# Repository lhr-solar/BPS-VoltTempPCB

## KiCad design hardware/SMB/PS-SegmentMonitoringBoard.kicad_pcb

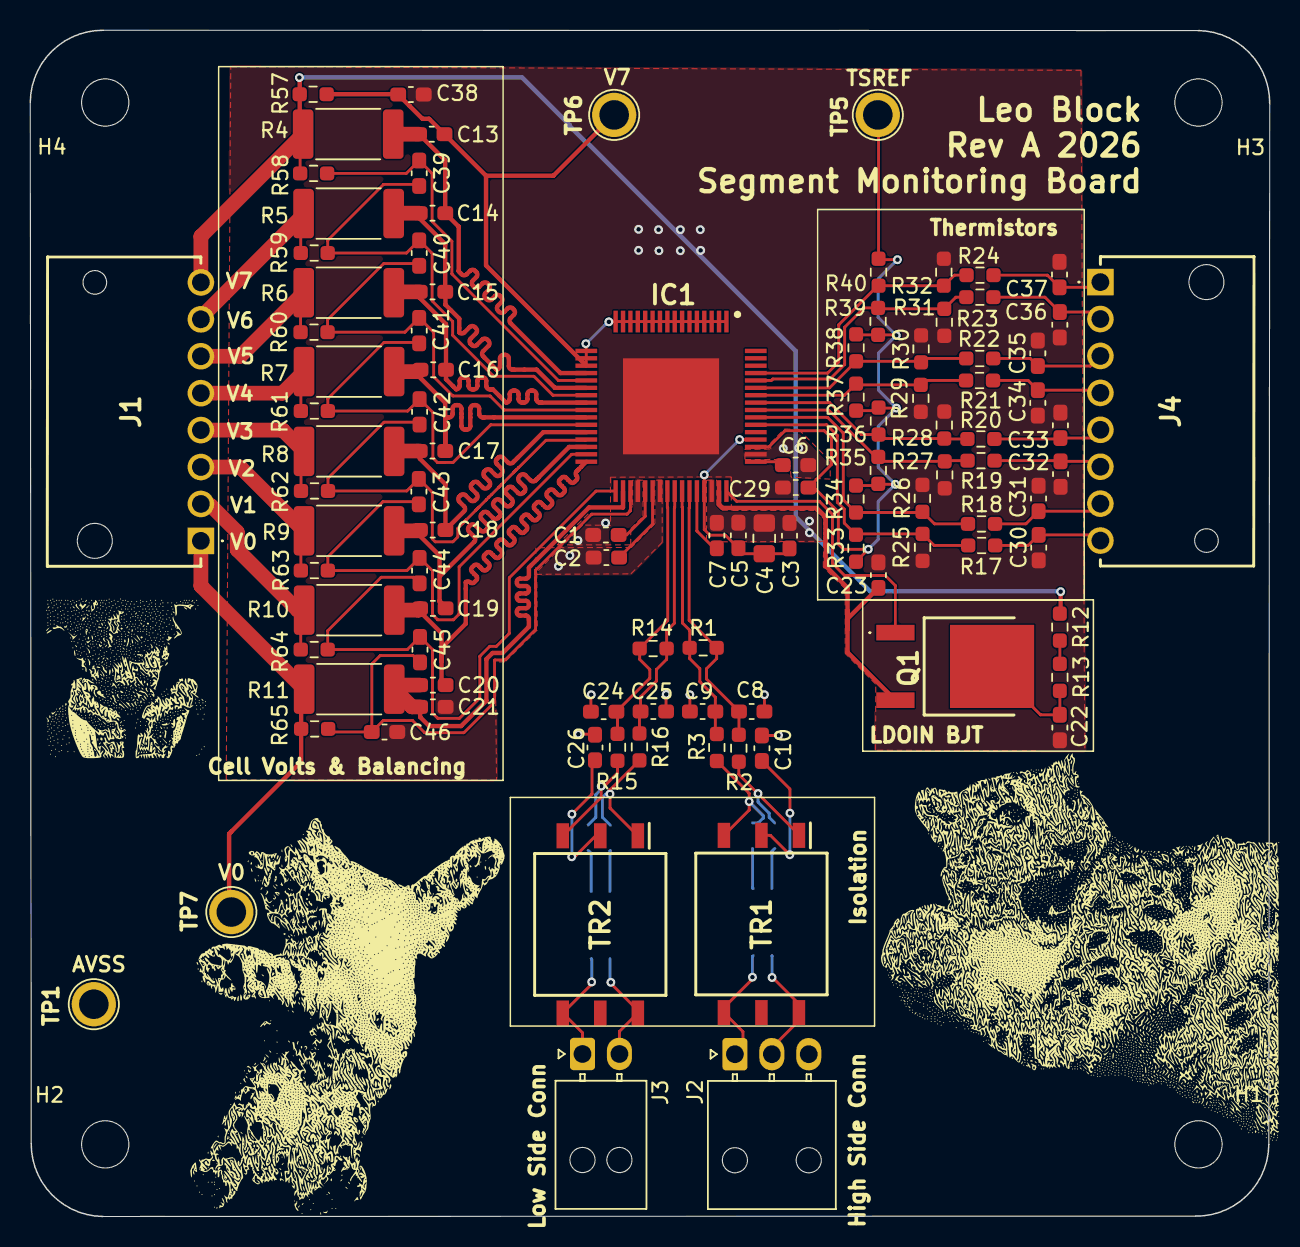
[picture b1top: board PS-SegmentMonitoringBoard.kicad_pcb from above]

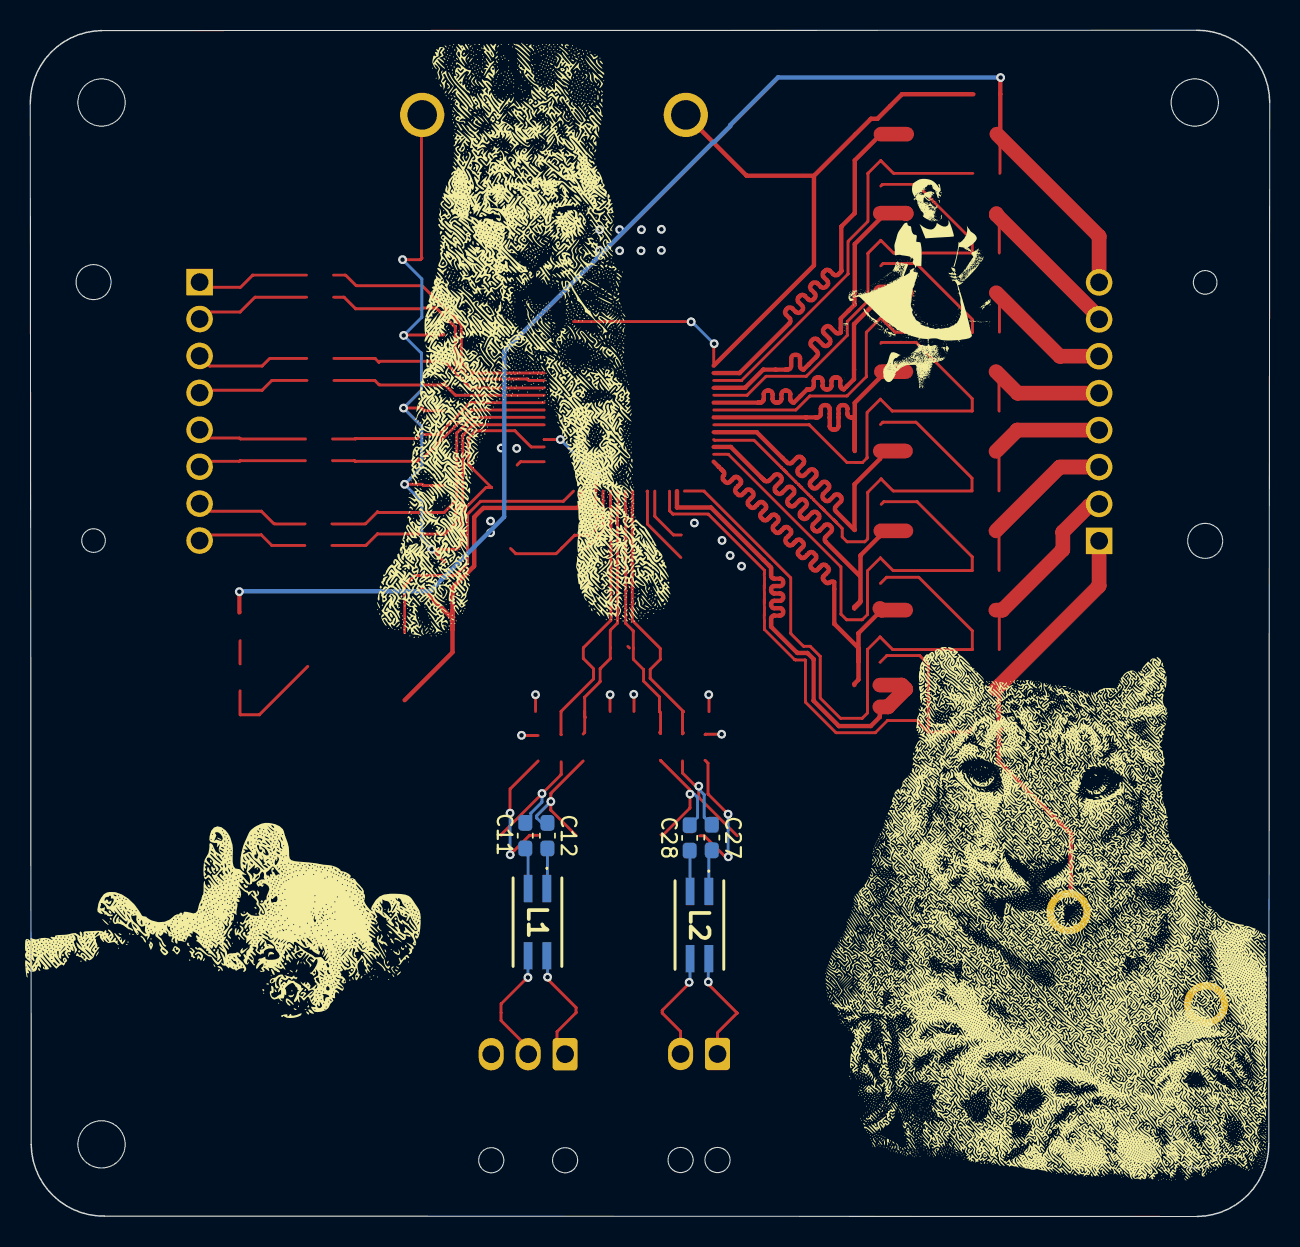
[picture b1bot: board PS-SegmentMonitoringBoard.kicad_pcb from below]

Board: 4 copper layers, 83.9 x 80.3 mm, 114 parts (6 on the bottom side), 70 nets.

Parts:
C1, C2, C29, C30, C31, C32, C33, C34, C35, C36, C37: 1uF; C_0603_1608Metric_Pad1.08x0.95mm_HandSolder
C3: 22nF; C_0603_1608Metric_Pad1.08x0.95mm_HandSolder
C4: 4.7uF; C_0805_2012Metric_Pad1.18x1.45mm_HandSolder
C5: 100nF; C_0603_1608Metric_Pad1.08x0.95mm_HandSolder
C6: 2.2uF; C_0603_1608Metric_Pad1.08x0.95mm_HandSolder
C7, C23: 0.1uF; C_0603_1608Metric_Pad1.08x0.95mm_HandSolder
C8, C9, C11, C12, C24, C25, C27, C28: 220pF; C_0603_1608Metric_Pad1.08x0.95mm_HandSolder
C10, C26: 100pF; C_0603_1608Metric_Pad1.08x0.95mm_HandSolder
C13, C14, C15, C16, C17, C18, C19, C20, C21, C39, C40, C41, C42, C43, C44, C45, C46: 0.47uF; C_0603_1608Metric_Pad1.08x0.95mm_HandSolder
C22: 0.22uF; C_0603_1608Metric_Pad1.08x0.95mm_HandSolder
C38: 10nF; C_0603_1608Metric_Pad1.08x0.95mm_HandSolder
H1, H2, H3, H4: MountingHole; MountingHole_3.2mm_M3
IC1: BQ79616PAPR; QFP50P1200X1200X120-65N
J1: voltTapsConn; Molex_Nano-Fit_105313-xx08_1x08_P2.50mm_Horizontal
J2: highSideConn; Molex_Nano-Fit_105313-xx03_1x03_P2.50mm_Horizontal
J3: lowSideConn; Molex_Nano-Fit_105313-xx02_1x02_P2.50mm_Horizontal
J4: thermsConn; Molex_Nano-Fit_105313-xx08_1x08_P2.50mm_Horizontal
L1, L2: L_Coupled_1423; 744242471
LOGO1: Dr. Hallock; LHRs_LOGO
Q1: ZXTN4004KTC
R1, R14, R17, R18, R19, R20, R21, R22, R23, R24: 1k; R_0603_1608Metric_Pad0.98x0.95mm_HandSolder
R2, R3, R15, R16: 49; R_0603_1608Metric_Pad0.98x0.95mm_HandSolder
R4, R5, R6, R7, R8, R9, R10, R11: 6.2; R_2512_6332Metric_Pad1.40x3.35mm_HandSolder
R12: 200; R_0603_1608Metric_Pad0.98x0.95mm_HandSolder
R13, R58, R59, R60, R61, R62, R63, R64, R65: 100; R_0603_1608Metric_Pad0.98x0.95mm_HandSolder
R25, R26, R27, R28, R29, R30, R31, R32: 15k; R_0603_1608Metric_Pad0.98x0.95mm_HandSolder
R33, R34, R35, R36, R37, R38, R39, R40: 3.6k; R_0603_1608Metric_Pad0.98x0.95mm_HandSolder
R57: 30; R_0603_1608Metric_Pad0.98x0.95mm_HandSolder
TP1: AVSS; TestPoint_Plated_Hole_D2.0mm
TP5: TSREF; TestPoint_Plated_Hole_D2.0mm
TP6: V7; TestPoint_Plated_Hole_D2.0mm
TP7: V0; TestPoint_Plated_Hole_D2.0mm
TR1, TR2: HMU1228NL; SOP254P1270X685-6N

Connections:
/CB0: C20.2, C21.1, IC1.34 (CB0), R11.2
/CB1: C19.2, C20.1, IC1.32 (CB1), R10.2
/CB2: C18.2, C19.1, IC1.30 (CB2), R9.2
/CB3: C17.2, C18.1, IC1.28 (CB3), R8.2
/CB4: C16.2, C17.1, IC1.26 (CB4), R7.2
/CB5: C15.2, C16.1, IC1.24 (CB5), R6.2
/CB6: C14.2, C15.1, IC1.22 (CB6), R5.2
/CB7: C13.2, C14.1, IC1.20 (CB7), R4.2
/CVDD: C3.1, C4.1, C5.1, IC1.45 (CVDD), IC1.52 (RX)
/Cell_Balancing/V0: J1.1, R11.1, R65.1, TP7.1 (1_1)
/Cell_Balancing/V1: J1.2, R10.1, R64.1
/Cell_Balancing/V2: J1.3, R9.1, R63.1
/Cell_Balancing/V3: J1.4, R8.1, R62.1
/Cell_Balancing/V4: J1.5, R7.1, R61.1
/Cell_Balancing/V5: J1.6, R6.1, R60.1
/Cell_Balancing/V6: J1.7, R5.1, R59.1
/Cell_Balancing/V7: J1.8, R4.1, R12.1, R57.2, R58.1
/LDOIN_NPN/LDOIN: C23.1, IC1.47 (LDOIN), Q1.3 (E)
/LDOIN_NPN/NPNB: IC1.48 (NPNB), Q1.1 (B)
/TSREF: C29.1, IC1.51 (TSREF), R33.2, R34.2, R35.2, R36.2, R37.2, R38.2, R39.2, R40.2, TP5.1 (1_1)
/Thermistors/NTC0: IC1.61 (GPIO1), R24.1, R32.2, R40.1
/Thermistors/NTC1: IC1.60 (GPIO2), R23.1, R31.2, R39.1
/Thermistors/NTC2: IC1.59 (GPIO3), R22.1, R30.2, R38.1
/Thermistors/NTC3: IC1.58 (GPIO4), R21.1, R29.2, R37.1
/Thermistors/NTC4: IC1.57 (GPIO5), R20.1, R28.2, R36.1
/Thermistors/NTC5: IC1.56 (GPIO6), R19.1, R27.2, R35.1
/Thermistors/NTC6: IC1.55 (GPIO7), R18.1, R26.2, R34.1
/Thermistors/NTC7: IC1.54 (GPIO8), R17.1, R25.2, R33.1
/Thermistors/TEMP_0: C37.1, J4.1, R24.2
/Thermistors/TEMP_1: C36.1, J4.2, R23.2
/Thermistors/TEMP_2: C35.1, J4.3, R22.2
/Thermistors/TEMP_3: C34.1, J4.4, R21.2
/Thermistors/TEMP_4: C33.1, J4.5, R20.2
/Thermistors/TEMP_5: C32.1, J4.6, R19.2
/Thermistors/TEMP_6: C31.1, J4.7, R18.2
/Thermistors/TEMP_7: C30.1, J4.8, R17.2
/Volt_Taps/VC0: C45.2, C46.1, IC1.35 (VC0), R65.2
/Volt_Taps/VC1: C44.2, C45.1, IC1.33 (VC1), R64.2
/Volt_Taps/VC2: C43.2, C44.1, IC1.31 (VC2), R63.2
/Volt_Taps/VC3: C42.2, C43.1, IC1.29 (VC3), R62.2
/Volt_Taps/VC4: C41.2, C42.1, IC1.27 (VC4), R61.2
/Volt_Taps/VC5: C40.2, C41.1, IC1.25 (VC5), R60.2
/Volt_Taps/VC6: C39.2, C40.1, IC1.23 (VC6), R59.2
/Volt_Taps/VC7: C39.1, IC1.21 (VC7), R58.2
/extraCells: C13.1, C38.2, IC1.1 (BAT), IC1.2 (CB16), IC1.3 (VC16), IC1.4 (CB15), IC1.5 (VC15), IC1.6 (CB14), IC1.7 (VC14), IC1.8 (CB13), IC1.9 (VC13), IC1.10 (CB12), IC1.11 (VC12), IC1.12 (CB11), IC1.13 (VC11), IC1.14 (CB10), IC1.15 (VC10), IC1.16 (CB9), IC1.17 (VC9), IC1.18 (CB8), IC1.19 (VC8), R57.1, TP6.1 (1_1)
/highSideIsolation/COMHN: C9.1, IC1.42 (COMHN), R1.2, R3.1
/highSideIsolation/COMHP: C8.1, IC1.43 (COMHP), R1.1, R2.1
/highSideIsolation/isolatedCOMHN: J2.1, L1.4, TR1.4
/highSideIsolation/isolatedCOMHP: J2.2, L1.3, TR1.6
/highSideIsolation/preIsolationCOMHN: C12.1, R3.2, TR1.3
/highSideIsolation/preIsolationCOMHP: C11.1, R2.2, TR1.1
/lowSideIsolation/COMLN: C25.1, IC1.41 (COMLN), R14.2, R16.1
/lowSideIsolation/COMLP: C24.1, IC1.40 (COMLP), R14.1, R15.1
/lowSideIsolation/isolatedCOMLN: J3.2, L2.3, TR2.6
/lowSideIsolation/isolatedCOMLP: J3.1, L2.4, TR2.4
/lowSideIsolation/preIsolationCOMHN: C28.1, R16.2, TR2.1
/lowSideIsolation/preIsolationCOMHP: C27.1, R15.2, TR2.3
AVSS: C1.2, C2.2, C3.2, C4.2, C5.2, C6.2, C7.1, C8.2, C9.2, C10.1, C21.2, C22.2, C23.2, C24.2, C25.2, C26.1, C29.2, C30.2, C31.2, C32.2, C33.2, C34.2, C35.2, C36.2, C37.2, C38.1, C46.2, IC1.36 (REFHM), IC1.39 (AVSS), IC1.46 (CVSS), IC1.50 (DVSS), IC1.65 (PAD), R25.1, R26.1, R27.1, R28.1, R29.1, R30.1, R31.1, R32.1, TP1.1 (1_1)
unnamed: C10.2, TR1.2
unnamed: C11.2, L1.2
unnamed: C12.2, L1.1
unnamed: C26.2, TR2.2
unnamed: C27.2, L2.1
unnamed: C28.2, L2.2
unnamed: C2.1, IC1.38 (AVDD)
unnamed: C6.1, IC1.49 (DVDD)
unnamed: C7.2, IC1.44 (NEG5V)
unnamed: C1.1, IC1.37 (REFHP)
unnamed: C22.1, Q1.2 (C), R13.2
unnamed: R12.2, R13.1

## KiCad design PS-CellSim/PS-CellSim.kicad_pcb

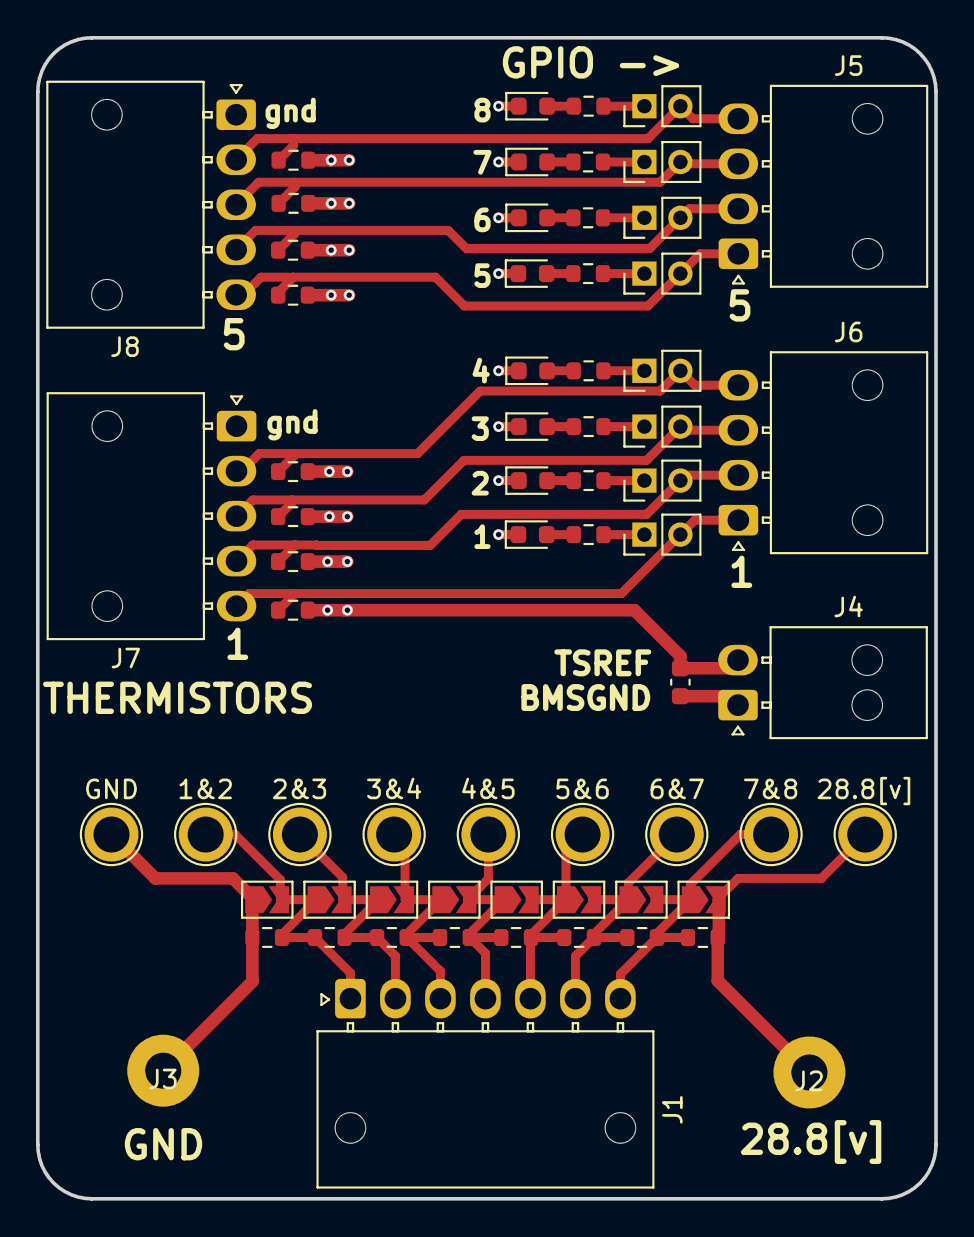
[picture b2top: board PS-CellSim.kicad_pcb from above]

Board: 2 copper layers, 49.9 x 64.5 mm, 66 parts (0 on the bottom side), 35 nets.

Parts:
1&2, 2&3, 3&4, 4&5, 5&6, 6&7, 7&8, 28.8[v]: TestPoint; TestPoint_Plated_Hole_D2.0mm
C1: 1 uF; C_0603_1608Metric
D1, D2, D3, D4, D5, D6, D7, D8: LED; LED_0603_1608Metric
GND: TestPoint; TestPoint_Plated_Hole_D2.0mm
J1: bms_taps; Molex_Nano-Fit_105313-xx07_1x07_P2.50mm_Horizontal
J2: bench_vcc; Banana_Jack_1_Pin_4mm
J3: bench_gnd; Banana_Jack_1_Pin_4mm
J4: bms_ref; Molex_Nano-Fit_105313-xx02_1x02_P2.50mm_Horizontal
J5: bms_gpio_set2; Molex_Nano-Fit_105313-xx04_1x04_P2.50mm_Horizontal
J6: bms_gpio_set1; Molex_Nano-Fit_105313-xx04_1x04_P2.50mm_Horizontal
J7: therm_set1; Molex_Nano-Fit_105313-xx05_1x05_P2.50mm_Horizontal
J8: therm_set2; Molex_Nano-Fit_105313-xx05_1x05_P2.50mm_Horizontal
JP1, JP2, JP3, JP4, JP5, JP6, JP7, JP8: SolderJumper_2_Open; SolderJumper-2_P1.3mm_Open_TrianglePad1.0x1.5mm
JP9, JP10, JP11, JP12, JP13, JP14, JP15, JP16: Jumper; PinHeader_1x02_P2.00mm_Vertical
R1, R2, R3, R4, R5, R6, R7, R8: 50Ω; R_0603_1608Metric
R9, R11, R13, R15, R17, R19, R21, R23: 10 kΩ; R_0603_1608Metric
R10, R12, R14, R16, R18, R20, R22, R24: 250 Ω; R_0603_1608Metric

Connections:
+5V: C1.1, J4.2, R9.1, R11.1, R13.1, R15.1, R17.1, R19.1, R21.1, R23.1
/1&2: 1&2.1 (1_1), J1.1, JP1.2 (B), JP2.1 (A), R1.1, R2.2
/2&3: 2&3.1 (1_1), J1.2, JP2.2 (B), JP3.1 (A), R2.1, R3.2
/3&4: 3&4.1 (1_1), J1.3, JP3.2 (B), JP4.1 (A), R3.1, R4.2
/4&5: 4&5.1 (1_1), J1.4, JP4.2 (B), JP5.1 (A), R4.1, R5.2
/5&6: 5&6.1 (1_1), J1.5, JP5.2 (B), JP6.1 (A), R5.1, R6.2
/6&7: 6&7.1 (1_1), J1.6, JP6.2 (B), JP7.1 (A), R6.1, R7.2
/7&8: 7&8.1 (1_1), J1.7, JP7.2 (B), JP8.1 (A), R7.1, R8.2
/GPIO1: J6.1, J7.5, JP9.2 (B), R9.2
/GPIO2: J6.2, J7.4, JP10.2 (B), R11.2
/GPIO3: J6.3, J7.3, JP11.2 (B), R13.2
/GPIO4: J6.4, J7.2, JP12.2 (B), R15.2
/GPIO5: J5.1, J8.5, JP13.2 (B), R17.2
/GPIO6: J5.2, J8.4, JP14.2 (B), R19.2
/GPIO7: J5.3, J8.3, JP15.2 (B), R21.2
/GPIO8: J5.4, J8.2, JP16.2 (B), R23.2
GND: GND.1 (1_1), J3.1 (Pin_1_1), JP1.1 (A), R1.2
GND1: C1.2, D1.1 (K), D2.1 (K), D3.1 (K), D4.1 (K), D5.1 (K), D6.1 (K), D7.1 (K), D8.1 (K), J4.1, J7.1, J8.1
unnamed: D1.2 (A), R10.1
unnamed: D2.2 (A), R12.1
unnamed: D3.2 (A), R14.1
unnamed: D4.2 (A), R16.1
unnamed: D5.2 (A), R18.1
unnamed: D6.2 (A), R20.1
unnamed: D7.2 (A), R22.1
unnamed: D8.2 (A), R24.1
unnamed: JP9.1 (A), R10.2
unnamed: JP10.1 (A), R12.2
unnamed: JP11.1 (A), R14.2
unnamed: JP12.1 (A), R16.2
unnamed: JP13.1 (A), R18.2
unnamed: JP14.1 (A), R20.2
unnamed: JP15.1 (A), R22.2
unnamed: JP16.1 (A), R24.2
VCC: 28.8[v].1 (1_1), J2.1 (Pin_1_1), JP8.2 (B), R8.1

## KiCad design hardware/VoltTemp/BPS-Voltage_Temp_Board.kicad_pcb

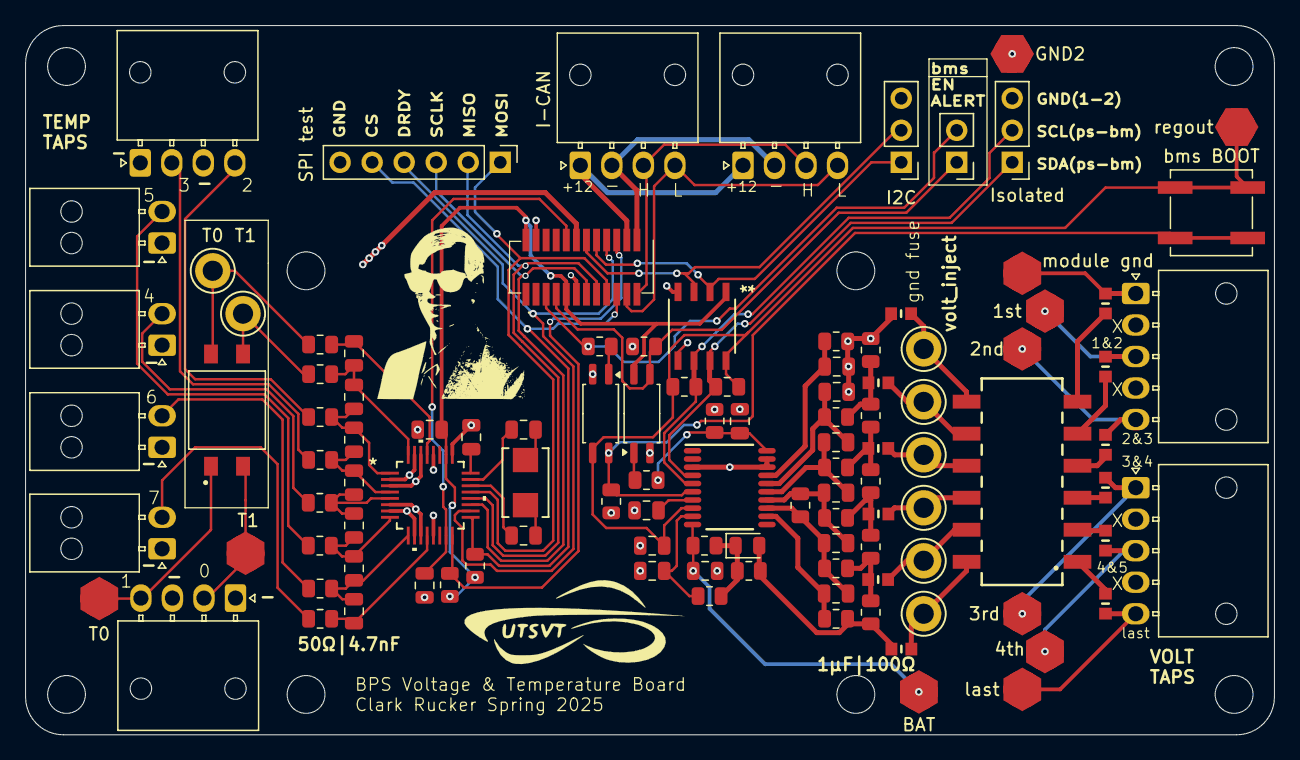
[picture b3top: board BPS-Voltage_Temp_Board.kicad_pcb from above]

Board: 2 copper layers, 99.0 x 56.2 mm, 115 parts (0 on the bottom side), 82 nets.

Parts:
1st: 1&2 COM; TestPoint_HEX_3mmID
2nd: 2&3 COM; TestPoint_HEX_3mmID
3rd: 3&4 COM; TestPoint_HEX_3mmID
4th: 4&5 COM; TestPoint_HEX_3mmID
BAT: BAT tap; TestPoint_HEX_3mmID
C1: 4.7pF; C_0805_2012Metric
C2: 10μF; C_0805_2012Metric
C3, C5, C6, C7, C8, C9, C10, C11, C19, C20: 1μF; C_0805_2012Metric
C4: 4.7μF; C_0805_2012Metric
C12, C13, C14, C15, C16, C17, C18: 4.7nF; C_0805_2012Metric
C21: 220nF; C_0805_2012Metric
C22, C23: 18pF; C_0805_2012Metric
D1: D_Zener_Small; D_0805_2012Metric
F1, F2, F3, F4, F5, F7, F8, F9, F10, F11: 10mA; ptc_fuse_FUSC1607X75N
F6, F12: 40mA; ptc_fuse_FUSC1607X75N
GND2: VSS tap; TestPoint_HEX_3mmID
H1, H1#2, H1#3, H1#4: MountingHole; MountingHole_3mm
I2C: psom bms i2c test; PinHeader_1x03_P2.54mm_Vertical
I-CAN: I-CAN connector; Molex_Nano-Fit_105313-xx04_1x04_P2.50mm_Horizontal
Isolated: bms i2c test; PinHeader_1x03_P2.54mm_Vertical
J1: VoltTap2; Molex_Nano-Fit_105313-xx05_1x05_P2.50mm_Horizontal
J2: VoltTap1; Molex_Nano-Fit_105313-xx05_1x05_P2.50mm_Horizontal
J6: I-CAN connector; Molex_Nano-Fit_105313-xx04_1x04_P2.50mm_Horizontal
J7: temptap0; Molex_Nano-Fit_105313-xx04_1x04_P2.50mm_Horizontal
J8: temptap1; Molex_Nano-Fit_105313-xx04_1x04_P2.50mm_Horizontal
J9: extratemp1; Molex_Nano-Fit_105313-xx02_1x02_P2.50mm_Horizontal
J10: extratemp3; Molex_Nano-Fit_105313-xx02_1x02_P2.50mm_Horizontal
J11: extratemp2; Molex_Nano-Fit_105313-xx02_1x02_P2.50mm_Horizontal
J12: extratemp4; Molex_Nano-Fit_105313-xx02_1x02_P2.50mm_Horizontal
J14: alert/en_test; PinHeader_1x02_P2.54mm_Vertical
R1, R6, R9, R10: 10kΩ; R_0805_2012Metric
R2: 500kΩ; R_0805_2012Metric
R3, R4, R17, R18, R19, R20, R21, R22: 100Ω; R_0805_2012Metric
R5: 2kΩ; R_0805_2012Metric
R7, R8: 1kΩ; R_0805_2012Metric
R11, R12, R13, R14, R15, R16: 0Ω; R_0805_2012Metric
R23, R24, R25, R26, R27, R28, R29, R30: 50Ω; R_0805_2012Metric
R31, R32: 100kΩ; R_0805_2012Metric
S1: 418121270806
S2: DS04-254-2-02BK-SMT-TR; SW_DS04-254-2-02BK-SMT-TR
SPI test: SPI test; PinHeader_1x06_P2.54mm_Vertical
T0: temp0inject; TestPoint_Keystone_5010-5014_Multipurpose
T0#2: t0test; TestPoint_HEX_3mmID
T1: temp1inject; TestPoint_Keystone_5010-5014_Multipurpose
T1#2: t1test; TestPoint_HEX_3mmID
TP9: last_inject; TestPoint_Keystone_5010-5014_Multipurpose
TP10: 4&5inject; TestPoint_Keystone_5010-5014_Multipurpose
TP11: 3&4inject; TestPoint_Keystone_5010-5014_Multipurpose
TP12: 2&3inject; TestPoint_Keystone_5010-5014_Multipurpose
TP13: 1&2inject; TestPoint_Keystone_5010-5014_Multipurpose
TP14: cellgndinject; TestPoint_Keystone_5010-5014_Multipurpose
U1, U3: EL3H7; SSOP-4_4.4x2.6mm_P1.27mm
U2: BQ7692003PW; PW0020A_N
U4: ISO1641BDR; SOIC8_D_TEX
U5: PeripheralSOM
U6: ADS131M08QPBSRQ1; TQFP32_PBS_TEX
XTAL1: ABM3-8.000MHZ-D2Y-T; XTAL_ABM3-8.000MHZ-D2Y-T_ABR
bms BOOT: BMS_BOOT; SW_SPST_B3SL-1002P
last: last_cell; TestPoint_HEX_3mmID
module gnd: GND2; TestPoint_HEX_3mmID
regout: regout testpoint; TestPoint_HEX_3mmID

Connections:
+3.3V: C20.1, R31.1, R32.2, U1.4, U4.1 (VCC1), U5.2 (+3.3V), U5.9 (+3.3V), U6.26 (DVDD)
+3.3VA: C19.1, U5.10 (VDDA(3.3V)), U6.15 (AVDD)
+12V: I-CAN.1 (12V), J6.1 (12V), U5.22 (+12V_In)
/1&2COM: F11.2, R15.2, R16.1, R21.2
/2&3COM: F10.2, R14.2, R15.1, R20.2
/3&4COM: F9.2, R13.2, R14.1, R19.2
/4&5COM: F8.2, R12.2, R13.1, R18.2
/BMSboot: R6.2, U2.6 (TS1), U3.4, bms BOOT.2
/DRDY: SPI test.4, U5.18 (PA2(ADC)), U6.18 (*DRDY)
/I-CAN_H: I-CAN.3 (CAN_H), J6.3 (CAN_H), U5.23 (CAN_H)
/I-CAN_L: I-CAN.4 (CAN_L), J6.4 (CAN_L), U5.21 (CAN_L)
/SYNC: R31.2, U5.20 (PA1(ADC)), U6.16 (*SYNC/*RESET)
/Thermistor town/AIN0: C18.1, R30.1, U6.29 (AIN0P)
/Thermistor town/AIN1: C17.1, C18.2, R29.1, U6.32 (AIN1P)
/Thermistor town/AIN2: C16.1, C17.2, R28.1, U6.1 (AIN2P)
/Thermistor town/AIN3: C15.1, C16.2, R27.1, U6.4 (AIN3P)
/Thermistor town/AIN4: C14.1, C15.2, R26.1, U6.5 (AIN4P)
/Thermistor town/AIN5: C13.1, C14.2, R25.1, U6.8 (AIN5P)
/Thermistor town/AIN6: C12.1, C13.2, R24.1, U6.9 (AIN6P)
/Thermistor town/AIN7: C12.2, R23.1, U6.12 (AIN7P)
/Thermistor town/temp0: R30.2, S2.1B, T0.1
/Thermistor town/temp1: R29.2, S2.2B, T1.1
/Thermistor town/temp2: J8.4, R28.2
/Thermistor town/temp3: J8.2, R27.2
/Thermistor town/temp4: J9.2, R26.2
/Thermistor town/temp5: J11.2, R25.2
/Thermistor town/temp6: J10.2, R24.2
/Thermistor town/temp7: J12.2, R23.2
/Thermistor town/xtal1: C22.2, U6.23 (XTAL1/CLKIN)
/Thermistor town/xtal2: C23.2, U6.22 (XTAL2)
/VC0: C11.1, R22.1, U2.17 (VC0)
/VC1: C9.1, C10.2, R21.1, U2.16 (VC1)
/VC2: C8.1, C9.2, R20.1, U2.15 (VC2)
/VC3: C7.1, C8.2, R11.1, R19.1, U2.14 (VC3)
/VC4: C6.1, C7.2, R11.2, R18.1, U2.13 (VC4)
/VC5: C6.2, R17.1, U2.12 (VC5)
/adCS: R32.1, SPI test.5, U5.19 (SPI1_NSS), U6.17 (*CS)
/adMISO: SPI test.2, U5.15 (SPI1_MISO), U6.20 (DOUT)
/adMOSI: SPI test.1, U5.17 (SPI1_MOSI), U6.21 (DIN)
/adSCLK: SPI test.3, U5.13 (SPI1_SCK), U6.19 (SCLK)
/bmSCL: Isolated.2, R10.1, U2.5 (SCL), U4.6 (SCL2)
/bmSDA: Isolated.1, R9.1, U2.4 (SDA), U4.7 (SDA2)
/bmsALERT: J14.1, R1.2, U1.3, U5.7 (SPI2_NSS)
/bmsEN: J14.2, R5.1, U5.5 (SPI2_SCK)
/last_cell: D1.2 (A), F7.2, R7.2, R12.1, R17.2
/psSCL: I2C.2, U4.3 (SCL1), U5.14 (I2C1_SCL)
/psSDA: I2C.1, U4.2 (SDA1), U5.16 (I2C1_SDA)
/regout: C4.2, R9.2, R10.2, U2.8 (REGOUT), U3.3, U4.8 (VCC2), bms BOOT.1, regout.1
GND: C20.2, C21.1, I2C.3, R1.1, SPI test.6, U3.2, U4.4 (GND1), U5.4 (GND), U5.11 (GND), U6.25 (DGND)
GND2: C1.1, C2.1, C3.1, C4.1, C5.1, C10.1, C11.2, F12.2, GND2.1, Isolated.3, R2.2, R6.1, R16.2, R22.2, U1.2, U2.3 (VSS), U2.18 (SRP), U2.19 (SRN), U4.5 (GND2)
GNDA: C19.2, J7.1, J7.3, J8.1, J8.3, J9.1, J10.1, J11.1, J12.1, U5.12 (GNDA), U6.2 (AIN2N), U6.3 (AIN3N), U6.6 (AIN4N), U6.7 (AIN5N), U6.10 (AIN6N), U6.11 (AIN7N), U6.13 (AGND), U6.28 (AGND), U6.30 (AIN0N), U6.31 (AIN1N)
GNDPWR: I-CAN.2 (GNDPWR), J6.2 (GNDPWR), U5.24 (GNDPWR)
unnamed: C22.1, XTAL1.2
unnamed: C23.1, XTAL1.1
unnamed: D1.1 (K), R4.2, R7.1, R8.2
unnamed: F1.1, S1.1
unnamed: F2.1, S1.2
unnamed: F3.1, S1.3
unnamed: F4.1, S1.4
unnamed: F5.1, S1.5
unnamed: F6.1, S1.6
unnamed: F7.1, S1.A1, TP9.1
unnamed: F8.1, S1.A2, TP10.1
unnamed: F9.1, S1.A3, TP11.1
unnamed: F10.1, S1.A4, TP12.1
unnamed: F11.1, S1.A5, TP13.1
unnamed: F12.1, S1.A6, TP14.1
unnamed: 3rd.1, F3.2, J1.1
unnamed: 4th.1, F2.2, J1.3
unnamed: F1.2, J1.5, last.1
unnamed: F6.2, J2.1, module gnd.1
unnamed: 1st.1, F5.2, J2.3
unnamed: 2nd.1, F4.2, J2.5
unnamed: J7.2, S2.2A, T1#2.1
unnamed: J7.4, S2.1A, T0#2.1
unnamed: R3.2, U1.1
unnamed: R5.2, U3.1
unnamed: C1.2, R2.1, R3.1, U2.20 (ALERT)
unnamed: BAT.1, C2.2, R4.1, U2.10 (BAT)
unnamed: C3.2, U2.7 (CAP1)
unnamed: C5.2, R8.1, U2.9 (REGSRC)
unnamed: C21.2, U6.24 (CAP)

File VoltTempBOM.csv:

Reference,Value,P/N,Datasheet,Footprint,Qty,DNP
C1,4.7pF,581-08052U4.7B,https://www.mouser.com/datasheet/2/40/U_Series-2942365.pdf,Capacitor_SMD:C_0805_2012Metric,1,
C2,10μF,TMK212BBJ106MGHT,https://www.mouser.com/ProductDetail/Taiyo-Yuden/TMK212BBJ10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,Capacitor_SMD:C_0805_2012Metric,1,
"C3,C5,C6,C7,C8,C9,C10,C11,C19,C20",1μF,C0805C105K5PACTU,https://www.mouser.com/ProductDetail/KEMET/C0805C105K5PACTU?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,Capacitor_SMD:C_0805_2012Metric,10,
C4,4.7μF,C0805C475K3RACAUTO,https://jlcpcb.com/partdetail/Kemet-C0805C475K3RACAUTO/C696371,Capacitor_SMD:C_0805_2012Metric,1,
"C12,C13,C14,C15,C16,C17,C18",4.7nF,80-C0805C472J3GAUTO ,https://www.mouser.com/datasheet/2/447/KEM_C1022_C0G_AUTO_SM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,Capacitor_SMD:C_0805_2012Metric,7,
C21,220nF,80-C0805C22JCRTU,https://www.mouser.com/datasheet/2/447/KEM_C1010_X7R_HV_SMD-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,Capacitor_SMD:C_0805_2012Metric,1,
"C22,C23",18pF,581-KGU21RCG2E180FU ,https://www.mouser.com/datasheet/2/40/KGU_Series-3454125.pdf,Capacitor_SMD:C_0805_2012Metric,2,
D1,D_Zener_Small,78-1N4448W-G3-08,https://www.vishay.com/docs/86363/1n448w-g.pdf,Diode_SMD:D_0805_2012Metric,1,
"F1,F2,F3,F4,F5,F7,F8,F9,F10,F11",10mA,FUSC1607X75N,~,UTSVT_Special:ptc_fuse_FUSC1607X75N,10,
"F6,F12",40mA,FUSC1607X75N,~,UTSVT_Special:ptc_fuse_FUSC1607X75N,2,
J1,VoltTap2,538-105313-1205,https://tools.molex.com/pdm_docs/sd/1053131205_sd.pdf,Connector_Molex:Molex_Nano-Fit_105313-xx05_1x05_P2.50mm_Horizontal,1,
J2,VoltTap1,538-105313-1205,https://tools.molex.com/pdm_docs/sd/1053131205_sd.pdf,Connector_Molex:Molex_Nano-Fit_105313-xx05_1x05_P2.50mm_Horizontal,1,
J3,psom bms i2c test,538-105313-1103 ,https://tools.molex.com/pdm_docs/sd/1053131103_sd.pdf,Connector_PinHeader_2.54mm:PinHeader_1x03_P2.54mm_Vertical,1,
J4,bms i2c test,538-105313-1103 ,https://tools.molex.com/pdm_docs/sd/1053131103_sd.pdf,Connector_PinHeader_2.54mm:PinHeader_1x03_P2.54mm_Vertical,1,
"J5,J6",I-CAN connector,538-105313-2104,https://tools.molex.com/pdm_docs/sd/1053132104_sd.pdf,Connector_Molex:Molex_Nano-Fit_105313-xx04_1x04_P2.50mm_Horizontal,2,
J7,temptap0,538-105313-2104,https://tools.molex.com/pdm_docs/sd/1053132104_sd.pdf,Connector_Molex:Molex_Nano-Fit_105313-xx04_1x04_P2.50mm_Horizontal,1,
J8,temptap1,538-105313-2104,https://tools.molex.com/pdm_docs/sd/1053132104_sd.pdf,Connector_Molex:Molex_Nano-Fit_105313-xx04_1x04_P2.50mm_Horizontal,1,
J9,extratemp1,538-105313-2102,https://tools.molex.com/pdm_docs/sd/1053132102_sd.pdf,Connector_Molex:Molex_Nano-Fit_105313-xx02_1x02_P2.50mm_Horizontal,1,
J10,extratemp3,538-105313-2102,https://tools.molex.com/pdm_docs/sd/1053132102_sd.pdf,Connector_Molex:Molex_Nano-Fit_105313-xx02_1x02_P2.50mm_Horizontal,1,
J11,extratemp2,538-105313-2102,https://tools.molex.com/pdm_docs/sd/1053132102_sd.pdf,Connector_Molex:Molex_Nano-Fit_105313-xx02_1x02_P2.50mm_Horizontal,1,
J12,extratemp4,538-105313-2102,https://tools.molex.com/pdm_docs/sd/1053132102_sd.pdf,Connector_Molex:Molex_Nano-Fit_105313-xx02_1x02_P2.50mm_Horizontal,1,
J13,SPI test,,~,Connector_PinHeader_2.54mm:PinHeader_1x06_P2.54mm_Vertical,1,
J14,alert/en_test,,~,Connector_PinHeader_2.54mm:PinHeader_1x02_P2.54mm_Vertical,1,
"R1,R6,R9,R10",10kΩ,CRCW080510K0FKEAC,https://www.mouser.com/ProductDetail/71-CRCW080510K0FKEAC,Resistor_SMD:R_0805_2012Metric,4,
R2,500kΩ,708-RNCF0805BTE500K,https://www.mouser.com/datasheet/2/385/SEI_RNCF-3077647.pdf,Resistor_SMD:R_0805_2012Metric,1,
"R3,R4,R17,R18,R19,R20,R21,R22",100Ω,594-MCU0805MD1000BP1,https://www.vishay.com/docs/28952/mcs0402at-mct0603at-mcu080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,Resistor_SMD:R_0805_2012Metric,8,
R5,2kΩ,667-ERJ-UP6D2001V ,https://www.mouser.com/catalog/specsheets/Panasonic_03-31-20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,Resistor_SMD:R_0805_2012Metric,1,
"R7,R8",1kΩ,CRCW08051K00FKEAC,https://www.mouser.com/ProductDetail/71-CRCW08051K00FKEAC,Resistor_SMD:R_0805_2012Metric,2,
"R11,R12,R13,R14,R15,R16",0Ω,SMD_0805,https://www.mouser.com/ProductDetail/71-CRCW08050000Z0ECC,Resistor_SMD:R_0805_2012Metric,6,
"R23,R24,R25,R26,R27,R28,R29,R30",50Ω,71-CRCW0805-50 ,https://www.vishay.com/docs/20008/dcrcw.pdf,Resistor_SMD:R_0805_2012Metric,8,
"R31,R32",100kΩ,CRCW0805100KFKEAC,https://www.mouser.com/ProductDetail/Vishay-Dale/CRCW0805100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,Resistor_SMD:R_0805_2012Metric,2,
S1,4.18121E+11,710-418121270806 ,https://www.we-online.com/components/products/datasheet/4181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,footprints:418121270806,1,
S2,DS04-254-2-02BK-SMT-TR,490-DS04254202BK-STR,https://www.mouser.com/datasheet/2/1628/ds04_254_smt-3510286.pdf,footprints:SW_DS04-254-2-02BK-SMT-TR,1,
SW1,BMS_BOOT,653-B3SL-1002P,https://www.mouser.com/datasheet/2/307/en-b3sl-1093544.pdf,Button_Switch_SMD:SW_SPST_B3SL-1002P,1,
TP2,last_cell,,~,UTSVT_Special:TestPoint_HEX_3mmID,1,
TP3,4&5 COM,,~,UTSVT_Special:TestPoint_HEX_3mmID,1,
TP4,3&4 COM,,~,UTSVT_Special:TestPoint_HEX_3mmID,1,
TP5,2&3 COM,,~,UTSVT_Special:TestPoint_HEX_3mmID,1,
TP6,1&2 COM,,~,UTSVT_Special:TestPoint_HEX_3mmID,1,
TP7,GND2,,~,UTSVT_Special:TestPoint_HEX_3mmID,1,
TP8,VSS tap,,~,UTSVT_Special:TestPoint_HEX_3mmID,1,
TP9,last_inject,,~,TestPoint:TestPoint_Keystone_5010-5014_Multipurpose,1,
TP10,4&5inject,,~,TestPoint:TestPoint_Keystone_5010-5014_Multipurpose,1,
TP11,3&4inject,,~,TestPoint:TestPoint_Keystone_5010-5014_Multipurpose,1,
TP12,2&3inject,,~,TestPoint:TestPoint_Keystone_5010-5014_Multipurpose,1,
TP13,1&2inject,,~,TestPoint:TestPoint_Keystone_5010-5014_Multipurpose,1,
TP14,cellgndinject,,~,TestPoint:TestPoint_Keystone_5010-5014_Multipurpose,1,
TP15,BAT tap,,~,UTSVT_Special:TestPoint_HEX_3mmID,1,
TP17,regout testpoint,,~,UTSVT_Special:TestPoint_HEX_3mmID,1,
TP19,t0test,,~,UTSVT_Special:TestPoint_HEX_3mmID,1,
TP20,t1test,,~,UTSVT_Special:TestPoint_HEX_3mmID,1,
TP21,temp0inject,,~,TestPoint:TestPoint_Keystone_5010-5014_Multipurpose,1,
TP22,temp1inject,,~,TestPoint:TestPoint_Keystone_5010-5014_Multipurpose,1,
"U1,U3",EL3H7,EL3H7DTAVG ,https://www.mouser.com/ProductDetail/Everlight/EL3H7DTA-VG?q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,Package_SO:SSOP-4_4.4x2.6mm_P1.27mm,2,
U2,BQ7692003PW,595-BQ7692000PWR ,https://www.ti.com/lit/ds/symlink/bq76920.pdf?ts=17389651031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,footprints:PW0020A_N,1,
U4,ISO1641BDR,595-ADS131M08QPBSRQ1,https://www.ti.com/lit/ds/symlink/iso1641.pdf?ts=17411477317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,footprints:SOIC8_D_TEX,1,
U5,PeripheralSOM,53307-2471,https://tools.molex.com/pdm_docs/sd/533072071_sd.pdf,UTSVT_Special:PeripheralSOM,1,
U6,ADS131M08QPBSRQ1,595-ADS131M08QPBSRQ1,https://www.ti.com/lit/ds/symlink/ads131m08-q1.pdf?ts=1738977833542,footprints:TQFP32_PBS_TEX,1,
XTAL1,ABM3-8.000MHZ-D2Y-T,815-ABM3-8-D2Y-T,https://www.mouser.com/datasheet/2/3/abm3-1774854.pdf,footprints:XTAL_ABM3-8.000MHZ-D2Y-T_ABR,1,

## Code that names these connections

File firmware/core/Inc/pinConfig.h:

#pragma once

#include "common.h"
#include "stm32xx_hal.h"

// Pin configuration for LEDs and heartbeat
//================================================================================
#define HEARTBEAT_PORT      GPIOB
#define HEARTBEAT_PIN       GPIO_PIN_11

#define BQ_HEARTBEAT_PORT   GPIOA
#define BQ_HEARTBEAT_PIN    GPIO_PIN_12

#define BQ_FAULT_PORT      GPIOA
#define BQ_FAULT_PIN       GPIO_PIN_11

#define BQ_RESET_PORT       GPIOB
#define BQ_RESET_PIN        GPIO_PIN_0

#define PSOM_LED1_PORT      GPIOA
#define PSOM_LED1_PIN       GPIO_PIN_7

#define PSOM_LED2_PORT      GPIOA
#define PSOM_LED2_PIN       GPIO_PIN_8

#define PSOM_LED3_PORT      GPIOA
#define PSOM_LED3_PIN       GPIO_PIN_15
//================================================================================

// Pin configuration for the broken out logic analzyer pins
//================================================================================
#define LOGIC_ANALZYER_CH1_PORT GPIOB
#define LOGIC_ANALZYER_CH1_PIN GPIO_PIN_3

#define LOGIC_ANALZYER_CH2_PORT GPIOB
#define LOGIC_ANALZYER_CH2_PIN GPIO_PIN_15

#define LOGIC_ANALZYER_CH4_PORT GPIOB
#define LOGIC_ANALZYER_CH4_PIN GPIO_PIN_14
//================================================================================



// Pin configuration for BQ I2C
//================================================================================
#define I2C_PORT            GPIOB
#define I2C_SCL_PIN         GPIO_PIN_6
#define I2C_SDA_PIN         GPIO_PIN_7
//================================================================================

// Pin configuration for ADC 
//================================================================================
// Temp 1 = ADC1_IN10 = PA5 
#define TEMP1_PORT            GPIOA
#define TEMP1_PIN             GPIO_PIN_5
// Temp 2 = ADC1_IN9 = PA4
#define TEMP2_PORT            GPIOA
#define TEMP2_PIN             GPIO_PIN_4
// Temp 3 = ADC1_IN7 = PA2
#define TEMP3_PORT            GPIOA
#define TEMP3_PIN             GPIO_PIN_2
// Temp 4 = ADC1_IN11 = PA6
#define TEMP4_PORT            GPIOA
#define TEMP4_PIN             GPIO_PIN_6
// Temp 5 = OPAMP1_VINP / ADC1_IN5 = PA0
#define TEMP5_PORT            GPIOA
#define TEMP5_PIN             GPIO_PIN_0
//================================================================================

// Pin configuration for BQ CAN 
//================================================================================
#define CAN_PORT            GPIOB
#define CAN_RX              GPIO_PIN_8
#define CAN_TX              GPIO_PIN_9
//================================================================================

// USART pins for PSOM
#define USART_PORT GPIOA
#define USART_TX_PIN GPIO_PIN_9
#define USART_RX_PIN GPIO_PIN_10

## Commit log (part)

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2025-02-13 initial push of thermistor schematic
2025-03-01 rough layout done -connectors are not fully chosen yet, nano for temp, ??? for volt taps
2025-03-05 Addressed some concerns
2025-03-05 Added test points pre DIP. Removed p-mos, per boot switch pdf. Cleaned up symbols.
2025-03-05 nothing changedgit add .git add . (do not look at commit history :))
2025-03-06 concerns from review council addressed
2025-03-09 schematic should be finished. Preliminary layout with changes from review
2025-03-12 most traces ok, need to add pwr for adc & gnd everywhere
2025-03-15 Preliminary schematic done. need to adjust silkscreen and what not
2025-03-15 1st layout done. silkscreen done. BOM added.
2025-03-17 i added my name
2025-03-18 has 3d models added now
2025-03-25 fixed the BOM
2025-03-25 fixed bom but this time its not in gitignore
2025-04-09 pcb3dmodel
2025-04-09 footprint 3d models
2025-04-11 funny render
2025-08-10 fix branches
2025-08-10 fix branches (#1)
2025-08-10 new folder structure
2025-08-11 refactored repo
2025-08-11 progress
2025-08-11 added kicad-bild
2025-08-11 fix footprint references
2025-08-11 wrote makefile
2025-08-11 pragma and config + extra fix for if no .vscode
2025-08-11 add .vscode to gitignore
2025-08-13 populated some led and gpio functions
2025-08-13 add compile commands to .gitignore
2025-08-13 lowercase
2025-08-13 fixed makefile for running tests
2025-08-14 more progress on schematic
2025-08-14 add scrutineering stuff
2025-08-14 clean up schematic a lil bit
